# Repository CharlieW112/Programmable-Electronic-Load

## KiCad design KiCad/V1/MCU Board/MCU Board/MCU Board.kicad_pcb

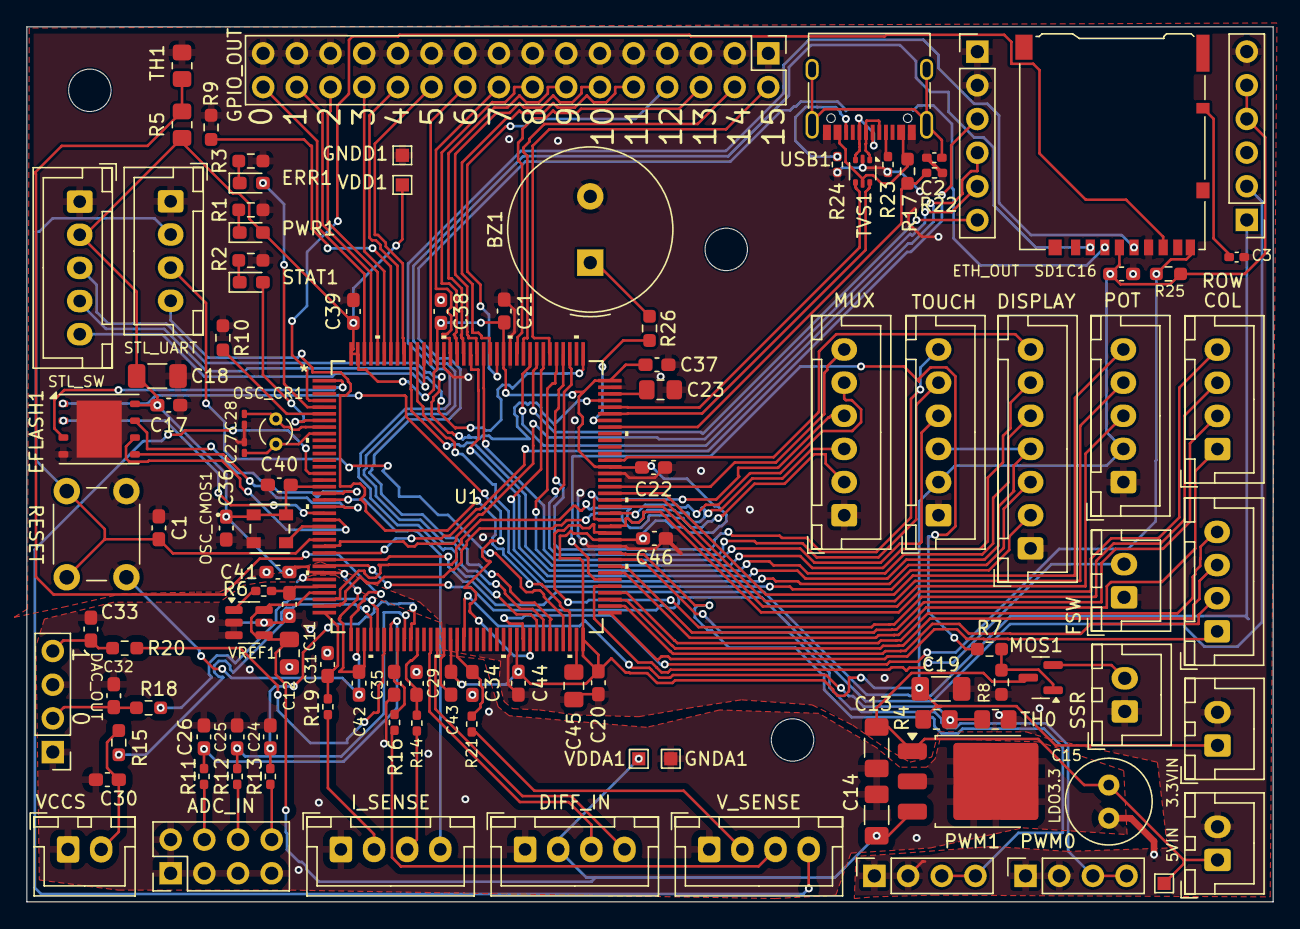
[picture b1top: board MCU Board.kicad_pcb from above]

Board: 2 copper layers, 94.0 x 66.0 mm, 114 parts (0 on the bottom side), 127 nets.

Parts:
3.3VIN, 5VIN: Conn_01x02; JST_XH_B2B-XH-A_1x02_P2.50mm_Vertical
5VIN2: TestPoint; TestPoint_Pad_1.0x1.0mm
ADC_IN: Conn_02x04_Odd_Even; PinHeader_2x04_P2.54mm_Vertical
BZ1: Buzzer; Buzzer_TDK_PS1240P02BT_D12.2mm_H6.5mm
C1: 100n; C_0603_1608Metric_Pad1.08x0.95mm_HandSolder
C2, C3: 10n; C_0402_1005Metric_Pad0.74x0.62mm_HandSolder
C11, C16, C17, C21, C22, C24, C25, C26, C29, C30, C31, C32, C33, C34, C35, C36, C37, C38, C39, C40, C41, C42, C43, C44, C45, C46: 0.1u; C_0603_1608Metric_Pad1.08x0.95mm_HandSolder
C12, C20, C23: 1u; C_0805_2012Metric_Pad1.18x1.45mm_HandSolder
C13, C14, C18, C19: 10u; C_1206_3216Metric_Pad1.33x1.80mm_HandSolder
C15: 100u; C_Radial_D6.3mm_H11.0mm_P2.50mm
C27, C28: 10p; C_0201_0603Metric_Pad0.64x0.40mm_HandSolder
COL: Conn_01x04; JST_XH_B4B-XH-A_1x04_P2.50mm_Vertical
DAC_OUT: Conn_01x04; PinHeader_1x04_P2.54mm_Vertical
DIFF_IN: Conn_01x04; JST_XH_B4B-XH-A_1x04_P2.50mm_Vertical
DISPLAY: Conn_01x07; JST_XH_B7B-XH-A_1x07_P2.50mm_Vertical
EFLASH1: W25Q128JVP; WSON-8-1EP_6x5mm_P1.27mm_EP3.4x4.3mm
ERR1: Red LED; D_0603_1608Metric_Pad1.05x0.95mm_HandSolder
ETH_OUT, ETH_OUT1: Conn_01x06; PinHeader_1x06_P2.54mm_Vertical
FSW: Conn_01x02; JST_XH_B2B-XH-A_1x02_P2.50mm_Vertical
GNDA1: TestPoint; TestPoint_Pad_1.0x1.0mm
GNDD1: TestPoint; TestPoint_Pad_1.0x1.0mm
GPIO_OUT: Conn_02x16_Odd_Even; PinHeader_2x16_P2.54mm_Vertical
H1, H2, H3: MountingHole; MountingHole_3.2mm_M3
I_SENSE: Conn_01x04; JST_XH_B4B-XH-A_1x04_P2.50mm_Vertical
LDO3.3: TO-252-3_TabPin2
MOS1: AO3400A; SOT-23
MUX: Conn_01x06; JST_XH_B6B-XH-A_1x06_P2.50mm_Vertical
NT1: NetTie_2; NetTie-2_SMD_Pad0.5mm
OSC_CMOS1: COM1305-25.000; SMD4_COM1305_2p5x3p2x1p0_RAL-M
OSC_CR1: AB26T-32.768KHZ; Crystal_C26-LF_D2.1mm_L6.5mm_Vertical
POT: Conn_01x05; JST_XH_B5B-XH-A_1x05_P2.50mm_Vertical
PWM0, PWM1: Conn_01x04; PinSocket_1x04_P2.54mm_Vertical
PWR1: Green LED; D_0603_1608Metric_Pad1.05x0.95mm_HandSolder
R1, R2, R3, R7: 1K; R_0603_1608Metric_Pad0.98x0.95mm_HandSolder
R4, R5: 10K 0.5%; R_0805_2012Metric_Pad1.20x1.40mm_HandSolder
R6: 10; R_0402_1005Metric_Pad0.72x0.64mm_HandSolder
R8, R10, R17, R25: 10K; R_0603_1608Metric_Pad0.98x0.95mm_HandSolder
R9: 10k; R_0603_1608Metric_Pad0.98x0.95mm_HandSolder
R11, R12, R13, R14, R16, R19, R21: 49.9; R_0402_1005Metric_Pad0.72x0.64mm_HandSolder
R15, R18, R20, R26: 100; R_0603_1608Metric_Pad0.98x0.95mm_HandSolder
R22: 20K; R_0402_1005Metric_Pad0.72x0.64mm_HandSolder
R23, R24: 5.1K; R_0402_1005Metric_Pad0.72x0.64mm_HandSolder
RESET: SW_Push; SW_PUSH_6mm_H9.5mm
ROW: Conn_01x04; JST_XH_B4B-XH-A_1x04_P2.50mm_Vertical
SD1: Micro_SD_Card_Det1; microSD_HC_Hirose_DM3AT-SF-PEJM5
SSR: Conn_01x02; JST_XH_B2B-XH-A_1x02_P2.50mm_Vertical
STAT1: Green LED; D_0603_1608Metric_Pad1.05x0.95mm_HandSolder
STL_SW: Conn_01x05; JST_XH_B5B-XH-A_1x05_P2.50mm_Vertical
STL_UART: Conn_01x04; JST_XH_B4B-XH-A_1x04_P2.50mm_Vertical
TH0, TH1: Thermistor_NTC; R_0805_2012Metric_Pad1.20x1.40mm_HandSolder
TOUCH: Conn_01x06; JST_XH_B6B-XH-A_1x06_P2.50mm_Vertical
TVS1: USBLC6-2P6; SOT-666
U1: STM32H7A3ZIT6; LQFP-144-M
USB1: USB_C_Receptacle_USB2.0_16P; USB_C_Receptacle_XKB_U262-16XN-4BVC11
VCCS: Conn_01x02; JST_XH_B2B-XH-A_1x02_P2.50mm_Vertical
VDD1: TestPoint; TestPoint_Pad_1.0x1.0mm
VDDA1: TestPoint; TestPoint_Pad_1.0x1.0mm
VREF1: MCP1501-33xCH; SOT-23-6
V_SENSE: Conn_01x04; JST_XH_B4B-XH-A_1x04_P2.50mm_Vertical

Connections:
3.3VREF: C11.1, R6.2, U1.32 (VREF+)
+5V: 5VIN.1, 5VIN2.1, C13.1, C15.1, LDO3.3.1 (IN), MOS1.3 (D)
/USB+: TVS1.3 (I/O2), USB1.A6 (D+), USB1.B6 (D+)
/USB-: TVS1.1 (I/O1), USB1.A7 (D-), USB1.B7 (D-)
ADC0_UNUSED: C26.1, R11.2, U1.43 (ADC0_UNUSED)
ADC1_UNUSED: C25.1, R12.2, U1.45 (ADC1_UNUSED)
ADC2_UNUSED: C24.1, R13.2, U1.46 (ADC2_UNUSED)
ADC_DIFF_N: DIFF_IN.4, U1.50 (ADC_DIFF_N)
ADC_DIFF_P: DIFF_IN.3, U1.49 (ADC_DIFF_P)
ADC_ISENSEC: C29.2, R14.1, U1.47 (ADC_ISENSEC)
ADC_ISENSEF: C31.1, R19.1, U1.36 (ADC_ISENSEF)
ADC_VCCSSENSE: C35.2, R16.1, U1.44 (ADC_VCCSSENSE)
ADC_VSENSE: C34.1, R21.1, U1.53 (ADC_VSENSE)
DAC0_UNUSED: R18.1, U1.41 (DAC0_UNUSED)
DAC1_UNUSED: R20.1, U1.42 (DAC1_UNUSED)
DAC_VCCS: R15.1, U1.40 (DAC_VCCS)
DISPL_CS: DISPLAY.2, U1.134 (DISPL_CS)
DISPL_DC: DISPLAY.6, U1.113 (DISPL_DC)
DISPL_LED: DISPLAY.7, U1.96 (DISPL_LED)
DISPL_MOSI: DISPLAY.5, U1.135 (DISPL_MOSI)
DISPL_RST: DISPLAY.3, U1.115 (DISPL_RST)
DISPL_SCK: DISPLAY.4, TOUCH.3, U1.126 (DISPL_SCK)
DTH2: R4.2, TH0.1, U1.54 (DTH2)
DTH3: R5.2, TH1.1, U1.37 (DTH3)
ENCODER_A: POT.3, U1.89 (ENCODER_A)
ENCODER_B: POT.4, U1.90 (ENCODER_B)
ENCODER_SW: POT.5, U1.91 (ENCODER_SW)
ERROR_LED: ERR1.2 (A), U1.5 (ERROR_LED)
ETH_CS: ETH_OUT.5, U1.26 (ETH_CS)
ETH_INT: ETH_OUT.6, U1.116 (ETH_INT)
ETH_MISO: ETH_OUT1.1, U1.28 (ETH_MISO)
ETH_MOSI: ETH_OUT.3, U1.27 (ETH_MOSI)
ETH_RST: ETH_OUT1.2, U1.29 (ETH_RST)
ETH_SCK: ETH_OUT.4, U1.117 (ETH_SCK)
E_FLASH_CLK: EFLASH1.6 (CLK), U1.22 (E_FLASH_CLK)
E_FLASH_CS: EFLASH1.1 (~CS), U1.64 (E_FLASH_CS)
E_FLASH_IO0: EFLASH1.5 (DI/IO_{0}), U1.20 (E_FLASH_IO0)
E_FLASH_IO1: EFLASH1.2 (DO/IO_{1}), U1.21 (E_FLASH_IO1)
E_FLASH_IO2: EFLASH1.3 (~WP/IO_{2}), U1.1 (E_FLASH_IO2)
E_FLASH_IO3: EFLASH1.7 (~HOLD/~RESET/IO_{3}), U1.18 (E_FLASH_IO3)
FRONT_SW: FSW.2, U1.77 (FRONT_SW)
GNDA: ADC_IN.1, ADC_IN.2, ADC_IN.3, ADC_IN.5, ADC_IN.7, C11.2, C12.2, C13.2, C14.2, C15.2, C24.2, C25.2, C26.2, C29.1, C30.1, C31.2, C32.1, C33.2, C34.2, C35.1, DAC_OUT.1, DAC_OUT.3, DIFF_IN.1, GNDA1.1, I_SENSE.1, LDO3.3.2 (GND), NT1.2, U1.31 (VSSA), VCCS.1, VREF1.2 (GND), VREF1.3 (GND), VREF1.5 (GND), V_SENSE.1
GNDD: 3.3VIN.2, 5VIN.2, BZ1.2 (-), C1.2, C2.2, C3.2, C16.1, C17.2, C18.2, C19.2, C20.2, C21.2, C22.2, C23.2, C27.2, C28.2, C36.2, C37.1, C38.1, C39.1, C40.1, C41.1, C42.1, C43.1, C44.1, C45.1, C46.1, DISPLAY.1, EFLASH1.4 (GND), EFLASH1.9 (EP), ETH_OUT.1, ETH_OUT.2, ETH_OUT1.6, FSW.1, GNDD1.1, GPIO_OUT.1, GPIO_OUT.3, GPIO_OUT.5, GPIO_OUT.7, GPIO_OUT.9, GPIO_OUT.11, GPIO_OUT.13, GPIO_OUT.15, GPIO_OUT.17, GPIO_OUT.19, GPIO_OUT.21, GPIO_OUT.23, GPIO_OUT.25, GPIO_OUT.27, GPIO_OUT.29, GPIO_OUT.31, MUX.1, NT1.1, OSC_CMOS1.2 (GND), POT.1, PWM0.1, PWM0.2, PWM1.1, PWM1.2, R1.2, R2.2, R3.2, R8.2, R9.2, R10.1, R22.2, R23.2, R24.2, RESET.2, SD1.6 (VSS), SSR.1, STL_SW.1, STL_UART.1, TH0.2, TH1.2, TOUCH.1, TVS1.2 (GND), U1.16 (VSS), U1.38 (VSS), U1.51 (VSS), U1.61 (VSS), U1.83 (VSS), U1.94 (VSS), U1.107 (VSS), U1.120 (VSS), U1.130 (VSS), USB1.A1 (GND), USB1.A12 (GND), USB1.B1 (GND), USB1.B12 (GND)
GPIO0_UNUSED: GPIO_OUT.32, U1.142 (GPIO0_UNUSED)
GPIO1_UNUSED: GPIO_OUT.30, U1.141 (GPIO1_UNUSED)
GPIO2_UNUSED: GPIO_OUT.28, U1.140 (GPIO2_UNUSED)
GPIO3_UNUSED: GPIO_OUT.26, U1.139 (GPIO3_UNUSED)
GPIO4_UNUSED: GPIO_OUT.24, U1.137 (GPIO4_UNUSED)
GPIO5_UNUSED: GPIO_OUT.22, U1.136 (GPIO5_UNUSED)
GPIO6_UNUSED: GPIO_OUT.20, U1.132 (GPIO6_UNUSED)
GPIO7_UNUSED: GPIO_OUT.18, U1.129 (GPIO7_UNUSED)
GPIO8_UNUSED: GPIO_OUT.16, U1.128 (GPIO8_UNUSED)
GPIO9_UNUSED: GPIO_OUT.14, U1.127 (GPIO9_UNUSED)
GPIO10_UNUSED: GPIO_OUT.12, U1.125 (GPIO10_UNUSED)
GPIO11_UNUSED: GPIO_OUT.10, U1.123 (GPIO11_UNUSED)
GPIO12_UNUSED: GPIO_OUT.8, U1.122 (GPIO12_UNUSED)
GPIO13_UNUSED: GPIO_OUT.6, U1.119 (GPIO13_UNUSED)
GPIO14_UNUSED: GPIO_OUT.4, U1.118 (GPIO14_UNUSED)
GPIO15_UNUSED: GPIO_OUT.2, U1.114 (GPIO15_UNUSED)
GPIO_I_SENSE_EN: I_SENSE.4, U1.19 (PF7)
GPIO_WARNING_HV: U1.15 (PF5), V_SENSE.4
HSE_OSC: OSC_CMOS1.3 (OUT), U1.23 (HSE_OSC)
MATC0: COL.1, U1.73 (MATC0)
MATC1: COL.2, U1.74 (MATC1)
MATC2: COL.3, U1.75 (MATC2)
MATC3: COL.4, U1.76 (MATC3)
MATR0: ROW.1, U1.79 (MATR0)
MATR1: ROW.2, U1.80 (MATR1)
MATR2: ROW.3, U1.85 (MATR2)
MATR3: ROW.4, U1.86 (MATR3)
MUX_A: MUX.4, U1.87 (PG2)
MUX_B: MUX.5, U1.88 (PG3)
MUX_C: MUX.6, U1.92 (PG7)
MUX_TH0: MUX.2, U1.35 (MUX_TH0)
MUX_TH1: MUX.3, U1.34 (MUX_TH1)
NRST: C1.1, RESET.1, STL_UART.2, U1.25 (NRST)
unnamed: ADC_IN.4, R11.1
unnamed: ADC_IN.6, R12.1
unnamed: ADC_IN.8, R13.1
unnamed: BZ1.1 (+), R26.2
unnamed: C32.2, DAC_OUT.2, R18.2
unnamed: C33.1, DAC_OUT.4, R20.2
unnamed: ERR1.1 (K), R3.1
unnamed: I_SENSE.2, R19.2
unnamed: I_SENSE.3, R14.2
unnamed: MOS1.1 (G), R7.2, R8.1
unnamed: PWR1.1 (K), R1.1
unnamed: C3.1, SD1.10 (SHIELD)
unnamed: R2.1, STAT1.1 (K)
unnamed: R17.1, TVS1.5 (VBUS), USB1.A4 (VBUS), USB1.A9 (VBUS), USB1.B4 (VBUS), USB1.B9 (VBUS)
unnamed: R10.2, U1.6 (VBAT)
unnamed: C20.1, U1.71 (VCAP)
unnamed: R9.1, U1.138 (BOOT0)
unnamed: C23.1, U1.106 (VCAP)
unnamed: R23.1, USB1.A5 (CC1)
unnamed: R24.1, USB1.B5 (CC2)
unnamed: C2.1, USB1.S1 (SHIELD)
unnamed: C30.2, R15.2, VCCS.2
unnamed: R6.1, VREF1.1 (OUT)
unnamed: R21.2, V_SENSE.2
unnamed: R16.2, V_SENSE.3
PWM0: PWM0.3, PWM0.4, U1.81 (PWM0)
PWM1: PWM1.3, PWM1.4, U1.82 (PWM1)
PWM_BUZZER: R26.1, U1.102 (PA10)
RTC_OSC_IN: C28.1, OSC_CR1.1, U1.8 (RTC_OSC_IN)
RTC_OSC_OUT: C27.1, OSC_CR1.2, U1.9 (RTC_OSC_OUT)
SD_CARD_DETECT: R25.1, SD1.9 (DET), U1.63 (SD_CARD_DETECT)
SD_CS: SD1.2 (DAT3/CD), U1.66 (SD_CS)
SD_MISO: SD1.7 (DAT0), U1.4 (SD_MISO)
SD_MOSI: SD1.3 (CMD), U1.67 (SD_MOSI)
SD_SCK: SD1.5 (CLK), U1.65 (SD_SCK)
SSR_EN: R7.1, U1.78 (SSR_EN)
SSR_OUT: MOS1.2 (S), SSR.2
STATUS_LED: STAT1.2 (A), U1.7 (STATUS_LED)
ST_LINK_RX: STL_UART.4, U1.70 (ST_LINK_RX)
ST_LINK_SWCLK: STL_SW.4, U1.109 (ST_LINK_SWCLK)
ST_LINK_SWDIO: STL_SW.3, U1.105 (ST_LINK_SWDIO)
ST_LINK_SWO: STL_SW.5, U1.133 (ST_LINK_SWO)
ST_LINK_TX: STL_UART.3, U1.69 (ST_LINK_TX)
TOUCH_CS: TOUCH.5, U1.111 (TOUCH_CS)
TOUCH_INT: TOUCH.6, U1.112 (TOUCH_INT)
TOUCH_MISO: TOUCH.4, U1.124 (TOUCH_MISO)
USB_DM: TVS1.6 (I/O1), U1.103 (USB_DM)
USB_DP: TVS1.4 (I/O2), U1.104 (USB_DP)
USB_VBUS: R17.2, R22.1, U1.101 (USB_VBUS)
VDD: 3.3VIN.1, C16.2, C17.1, C18.1, C19.1, C21.1, C22.1, C36.1, C37.2, C38.2, C39.2, C40.2, C41.2, C42.2, C43.2, C44.2, C45.2, C46.2, EFLASH1.8 (VCC), ETH_OUT1.4, ETH_OUT1.5, OSC_CMOS1.1 (EN), OSC_CMOS1.4 (Vdd), POT.2, PWR1.2 (A), R4.1, R5.1, R25.2, SD1.4 (VDD), STL_SW.2, TOUCH.2, U1.17 (VDD), U1.30 (VDD), U1.39 (VDD), U1.52 (VDD), U1.62 (VDD), U1.72 (VDD), U1.84 (VDD), U1.95 (VDD33USB), U1.108 (VDD), U1.121 (VDDMMC), U1.131 (VDD), U1.143 (PDR_ON), U1.144 (VDD), VDD1.1
VDDA: C12.1, C14.1, DIFF_IN.2, LDO3.3.3 (OUT), U1.33 (VDDA), VDDA1.1, VREF1.4 (~SHDN), VREF1.6 (VDD)

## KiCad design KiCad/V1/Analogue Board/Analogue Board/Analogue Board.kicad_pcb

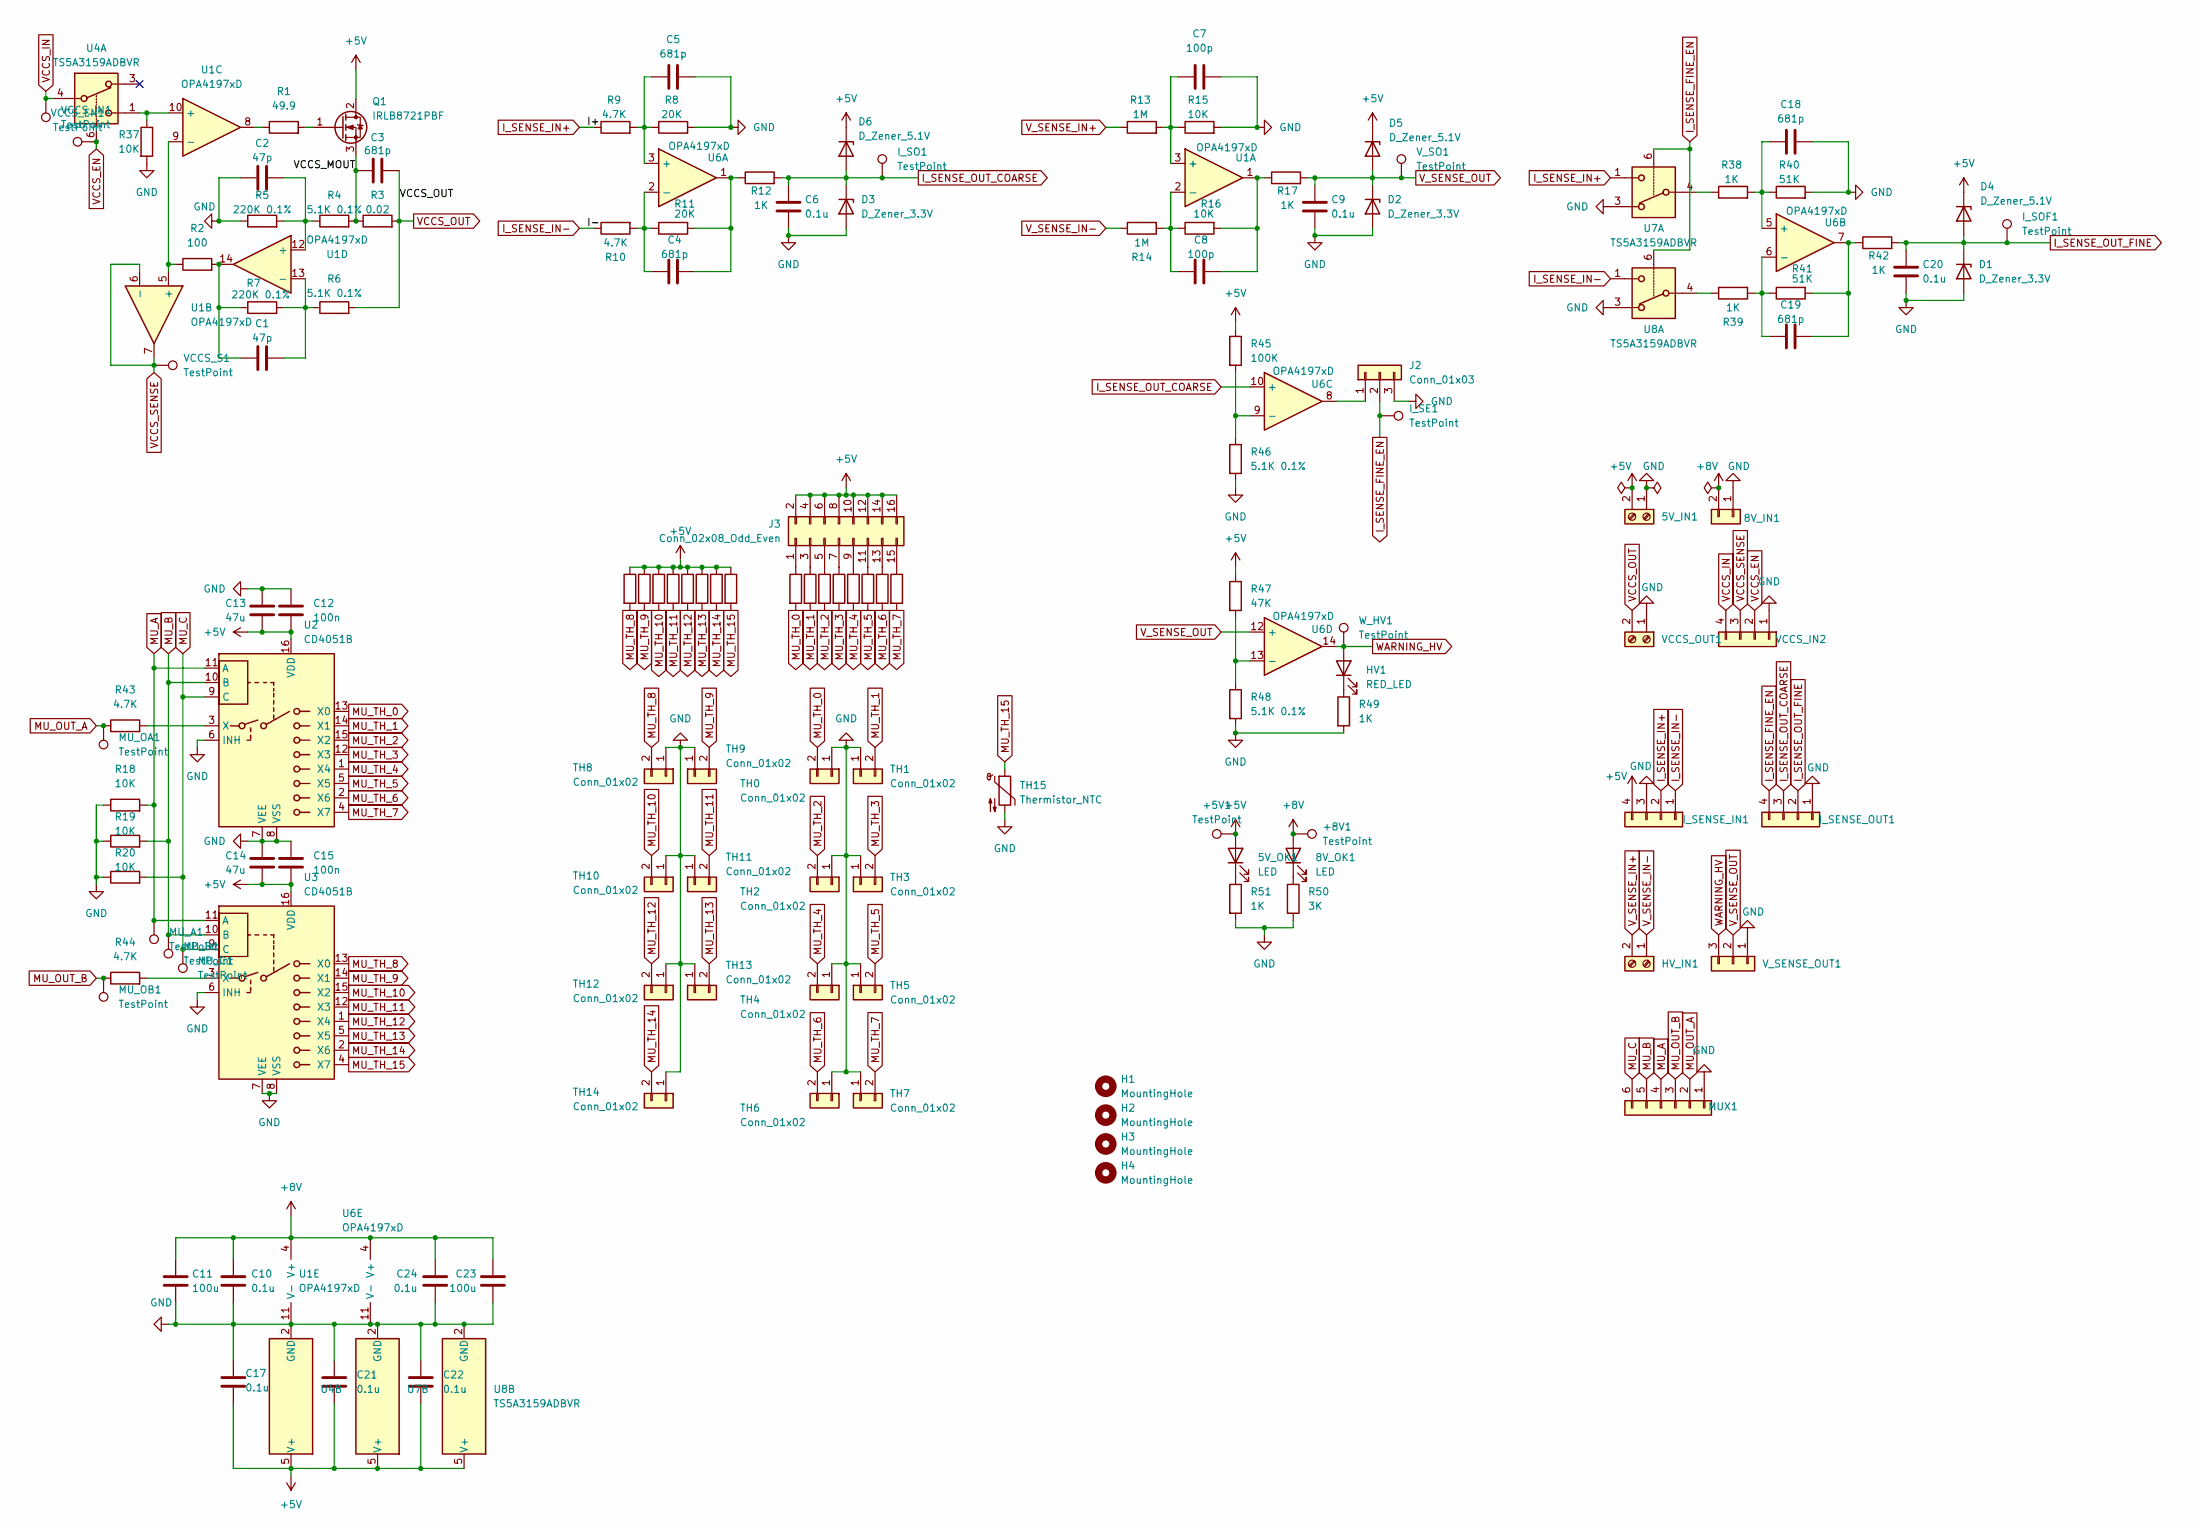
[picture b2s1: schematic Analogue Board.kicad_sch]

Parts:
5V_IN1: Screw_Terminal_01x02; TerminalBlock_bornier-2_P5.08mm
5V_OK1, 8V_OK1: LED; D_0603_1608Metric_Pad1.05x0.95mm_HandSolder
8V_IN1: Conn_01x02; JST_XH_B2B-XH-A_1x02_P2.50mm_Vertical
+5V1, +8V1: TestPoint; TestPoint_Pad_1.5x1.5mm
C1, C2: 47p; C_0201_0603Metric_Pad0.64x0.40mm_HandSolder
C3, C4, C5, C18, C19: 681p; C_0201_0603Metric_Pad0.64x0.40mm_HandSolder
C6, C9, C10, C17, C20, C21, C22, C24: 0.1u; C_0603_1608Metric_Pad1.08x0.95mm_HandSolder
C7, C8: 100p; C_0402_1005Metric_Pad0.74x0.62mm_HandSolder
C11, C23: 100u; C_Radial_D6.3mm_H11.0mm_P2.50mm
C12, C15: 100n; C_0603_1608Metric_Pad1.08x0.95mm_HandSolder
C13, C14: 47u; C_Radial_D6.3mm_H11.0mm_P2.50mm
D1, D2, D3: D_Zener_3.3V; D_SOD-123
D4, D5, D6: D_Zener_5.1V; D_SOD-123
H1, H2, H3, H4: MountingHole; MountingHole_3.2mm_M3
HV1: RED_LED; D_0603_1608Metric_Pad1.05x0.95mm_HandSolder
HV_IN1: Screw_Terminal_01x02; TerminalBlock_bornier-2_P5.08mm
I_SE1: TestPoint; TestPoint_Pad_1.5x1.5mm
I_SENSE_IN1: Conn_01x04; JST_XH_B4B-XH-A_1x04_P2.50mm_Vertical
I_SENSE_OUT1: Conn_01x04; JST_XH_B4B-XH-A_1x04_P2.50mm_Vertical
I_SO1: TestPoint; TestPoint_Pad_1.5x1.5mm
I_SOF1: TestPoint; TestPoint_Pad_1.5x1.5mm
J2: Conn_01x03; PinHeader_1x03_P2.54mm_Vertical
J3: Conn_02x08_Odd_Even; PinHeader_2x08_P2.54mm_Vertical
MUX1: Conn_01x06; JST_XH_B6B-XH-A_1x06_P2.50mm_Vertical
MU_A1: TestPoint; TestPoint_Pad_1.5x1.5mm
MU_B1: TestPoint; TestPoint_Pad_1.5x1.5mm
MU_C1: TestPoint; TestPoint_Pad_1.5x1.5mm
MU_OA1: TestPoint; TestPoint_Pad_1.5x1.5mm
MU_OB1: TestPoint; TestPoint_Pad_1.5x1.5mm
Q1: IRLB8721PBF; TO-220-3_Vertical
R1: 49.9; R_0402_1005Metric_Pad0.72x0.64mm_HandSolder
R2: 100; R_0603_1608Metric_Pad0.98x0.95mm_HandSolder
R3: 0.02; R_2010_5025Metric_Pad1.40x2.65mm_HandSolder
R4, R6, R46, R48: 5.1K 0.1%; R_0603_1608Metric_Pad0.98x0.95mm_HandSolder
R5, R7: 220K 0.1%; R_0805_2012Metric_Pad1.20x1.40mm_HandSolder
R8, R11: 20K; R_0402_1005Metric_Pad0.72x0.64mm_HandSolder
R9, R10, R43, R44: 4.7K; R_0603_1608Metric_Pad0.98x0.95mm_HandSolder
R12, R17, R38, R39, R42, R49, R51: 1K; R_0603_1608Metric_Pad0.98x0.95mm_HandSolder
R13, R14: 1M; R_Axial_DIN0207_L6.3mm_D2.5mm_P7.62mm_Horizontal
R15, R16, R18, R19, R20, R37: 10K; R_0603_1608Metric_Pad0.98x0.95mm_HandSolder
R21, R22, R23, R24, R25, R26, R27, R28, R29, R30, R31, R32, R33, R34, R35, R36: 10K 0.5%; R_0805_2012Metric_Pad1.20x1.40mm_HandSolder
R40, R41: 51K; R_0603_1608Metric_Pad0.98x0.95mm_HandSolder
R45: 100K; R_0402_1005Metric_Pad0.72x0.64mm_HandSolder
R47: 47K; R_0603_1608Metric_Pad0.98x0.95mm_HandSolder
R50: 3K; R_0603_1608Metric_Pad0.98x0.95mm_HandSolder
TH0, TH1, TH2, TH3, TH4, TH5, TH6, TH7, TH8, TH9, TH10, TH11, TH12, TH13, TH14: Conn_01x02; JST_XH_B2B-XH-A_1x02_P2.50mm_Vertical
TH15: Thermistor_NTC; R_0805_2012Metric_Pad1.20x1.40mm_HandSolder
U1, U6: OPA4197xD; SOIC-14_3.9x8.7mm_P1.27mm
U2, U3: CD4051B; DIP-16_W7.62mm
U4, U7, U8: TS5A3159ADBVR; SOT-23-6
VCCS_EN1: TestPoint; TestPoint_Pad_1.5x1.5mm
VCCS_IN1: TestPoint; TestPoint_Pad_1.5x1.5mm
VCCS_IN2: Conn_01x04; JST_XH_B4B-XH-A_1x04_P2.50mm_Vertical
VCCS_OUT1: Screw_Terminal_01x02; TerminalBlock_bornier-2_P5.08mm
VCCS_S1: TestPoint; TestPoint_Pad_1.5x1.5mm
V_SENSE_OUT1: Conn_01x03; JST_XH_B3B-XH-A_1x03_P2.50mm_Vertical
V_SO1: TestPoint; TestPoint_Pad_1.5x1.5mm
W_HV1: TestPoint; TestPoint_Pad_1.5x1.5mm

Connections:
+5V: 5V_IN1.2, 5V_OK1.2 (A), +5V1.1, C12.2, C13.2, C14.2, C15.2, C17.2, C21.2, C22.2, D4.1 (K), D5.1 (K), D6.1 (K), I_SENSE_IN1.4, J3.2, J3.4, J3.6, J3.8, J3.10, J3.12, J3.14, J3.16, Q1.2 (D), R29.1, R30.1, R31.1, R32.1, R33.1, R34.1, R35.1, R36.1, R45.1, R47.1, U2.16 (VDD), U3.16 (VDD), U4.5 (V+), U7.5 (V+), U8.5 (V+)
+8V: 8V_IN1.2, 8V_OK1.2 (A), +8V1.1, C10.1, C11.1, C23.1, C24.1, U1.4 (V+), U6.4 (V+)
/VCCS_MOUT: C3.1, Q1.3 (S), R3.1, R4.2
GND: 5V_IN1.1, 8V_IN1.1, C2.1, C5.2, C6.2, C7.2, C9.2, C10.2, C11.2, C12.1, C13.1, C14.1, C15.1, C17.1, C18.2, C20.2, C21.1, C22.1, C23.2, C24.2, D1.2 (A), D2.2 (A), D3.2 (A), I_SENSE_IN1.3, I_SENSE_OUT1.1, J2.3, MUX1.1, R5.1, R8.2, R15.2, R18.1, R19.1, R20.1, R37.2, R40.2, R46.2, R48.2, R49.2, R50.2, R51.2, TH0.1, TH1.1, TH2.1, TH3.1, TH4.1, TH5.1, TH6.1, TH7.1, TH8.1, TH9.1, TH10.1, TH11.1, TH12.1, TH13.1, TH14.1, TH15.2, U1.11 (V-), U2.6 (INH), U2.7 (VEE), U2.8 (VSS), U3.6 (INH), U3.7 (VEE), U3.8 (VSS), U4.2 (GND), U6.11 (V-), U7.2 (GND), U7.3, U8.2 (GND), U8.3, VCCS_IN2.1, VCCS_OUT1.1, V_SENSE_OUT1.1
I_SENSE_FINE_EN: I_SE1.1, I_SENSE_OUT1.4, J2.2, U7.6, U8.6
I_SENSE_IN+: I_SENSE_IN1.2, R9.1, U7.1
I_SENSE_IN-: I_SENSE_IN1.1, R10.1, U8.1
I_SENSE_OUT_COARSE: C6.1, D3.1 (K), D6.2 (A), I_SENSE_OUT1.3, I_SO1.1, R12.2, U6.10 (+)
I_SENSE_OUT_FINE: C20.1, D1.1 (K), D4.2 (A), I_SENSE_OUT1.2, I_SOF1.1, R42.2
MU_A: MUX1.4, MU_A1.1, R18.2, U2.11 (A), U3.11 (A)
MU_B: MUX1.5, MU_B1.1, R19.2, U2.10 (B), U3.10 (B)
MU_C: MUX1.6, MU_C1.1, R20.2, U2.9 (C), U3.9 (C)
MU_OUT_A: MUX1.2, MU_OA1.1, R43.1
MU_OUT_B: MUX1.3, MU_OB1.1, R44.1
MU_TH_0: R21.2, TH0.2, U2.13 (X0)
MU_TH_1: R22.2, TH1.2, U2.14 (X1)
MU_TH_2: R23.2, TH2.2, U2.15 (X2)
MU_TH_3: R24.2, TH3.2, U2.12 (X3)
MU_TH_4: R25.2, TH4.2, U2.1 (X4)
MU_TH_5: R26.2, TH5.2, U2.5 (X5)
MU_TH_6: R27.2, TH6.2, U2.2 (X6)
MU_TH_7: R28.2, TH7.2, U2.4 (X7)
MU_TH_8: R29.2, TH8.2, U3.13 (X0)
MU_TH_9: R30.2, TH9.2, U3.14 (X1)
MU_TH_10: R31.2, TH10.2, U3.15 (X2)
MU_TH_11: R32.2, TH11.2, U3.12 (X3)
MU_TH_12: R33.2, TH12.2, U3.1 (X4)
MU_TH_13: R34.2, TH13.2, U3.5 (X5)
MU_TH_14: R35.2, TH14.2, U3.2 (X6)
MU_TH_15: R36.2, TH15.1, U3.4 (X7)
unnamed: 5V_OK1.1 (K), R51.1
unnamed: 8V_OK1.1 (K), R50.1
unnamed: C1.1, R2.2, R7.1, U1.14
unnamed: C4.2, R11.2, R12.1, U6.1
unnamed: C8.2, R16.2, R17.1, U1.1
unnamed: C19.2, R41.2, R42.1, U6.7
unnamed: HV1.1 (K), R49.1
unnamed: J2.1, U6.8
unnamed: J3.1, R21.1
unnamed: J3.3, R22.1
unnamed: J3.5, R23.1
unnamed: J3.7, R24.1
unnamed: J3.9, R25.1
unnamed: J3.11, R26.1
unnamed: J3.13, R27.1
unnamed: J3.15, R28.1
unnamed: Q1.1 (G), R1.2
unnamed: R1.1, U1.8
unnamed: R38.1, U7.4
unnamed: R39.1, U8.4
unnamed: C7.1, R13.2, R15.1, U1.3 (+)
unnamed: C8.1, R14.2, R16.1, U1.2 (-)
unnamed: R2.1, U1.5 (+), U1.9 (-)
unnamed: R37.1, U1.10 (+), U4.1
unnamed: C2.2, R4.1, R5.2, U1.12 (+)
unnamed: C1.2, R6.1, R7.2, U1.13 (-)
unnamed: R43.2, U2.3 (X)
unnamed: R44.2, U3.3 (X)
unnamed: C5.1, R8.1, R9.2, U6.3 (+)
unnamed: C4.1, R10.2, R11.1, U6.2 (-)
unnamed: C18.1, R38.2, R40.1, U6.5 (+)
unnamed: C19.1, R39.2, R41.1, U6.6 (-)
unnamed: R45.2, R46.1, U6.9 (-)
unnamed: R47.2, R48.1, U6.13 (-)
VCCS_EN: U4.6, VCCS_EN1.1, VCCS_IN2.2
VCCS_IN: U4.4, VCCS_IN1.1, VCCS_IN2.4
VCCS_OUT: C3.2, R3.2, R6.2, VCCS_OUT1.2
VCCS_SENSE: U1.6 (-), U1.7, VCCS_IN2.3, VCCS_S1.1
V_SENSE_IN+: HV_IN1.2, R13.1
V_SENSE_IN-: HV_IN1.1, R14.1
V_SENSE_OUT: C9.1, D2.1 (K), D5.2 (A), R17.2, U6.12 (+), V_SENSE_OUT1.2, V_SO1.1
WARNING_HV: HV1.2 (A), U6.14, V_SENSE_OUT1.3, W_HV1.1

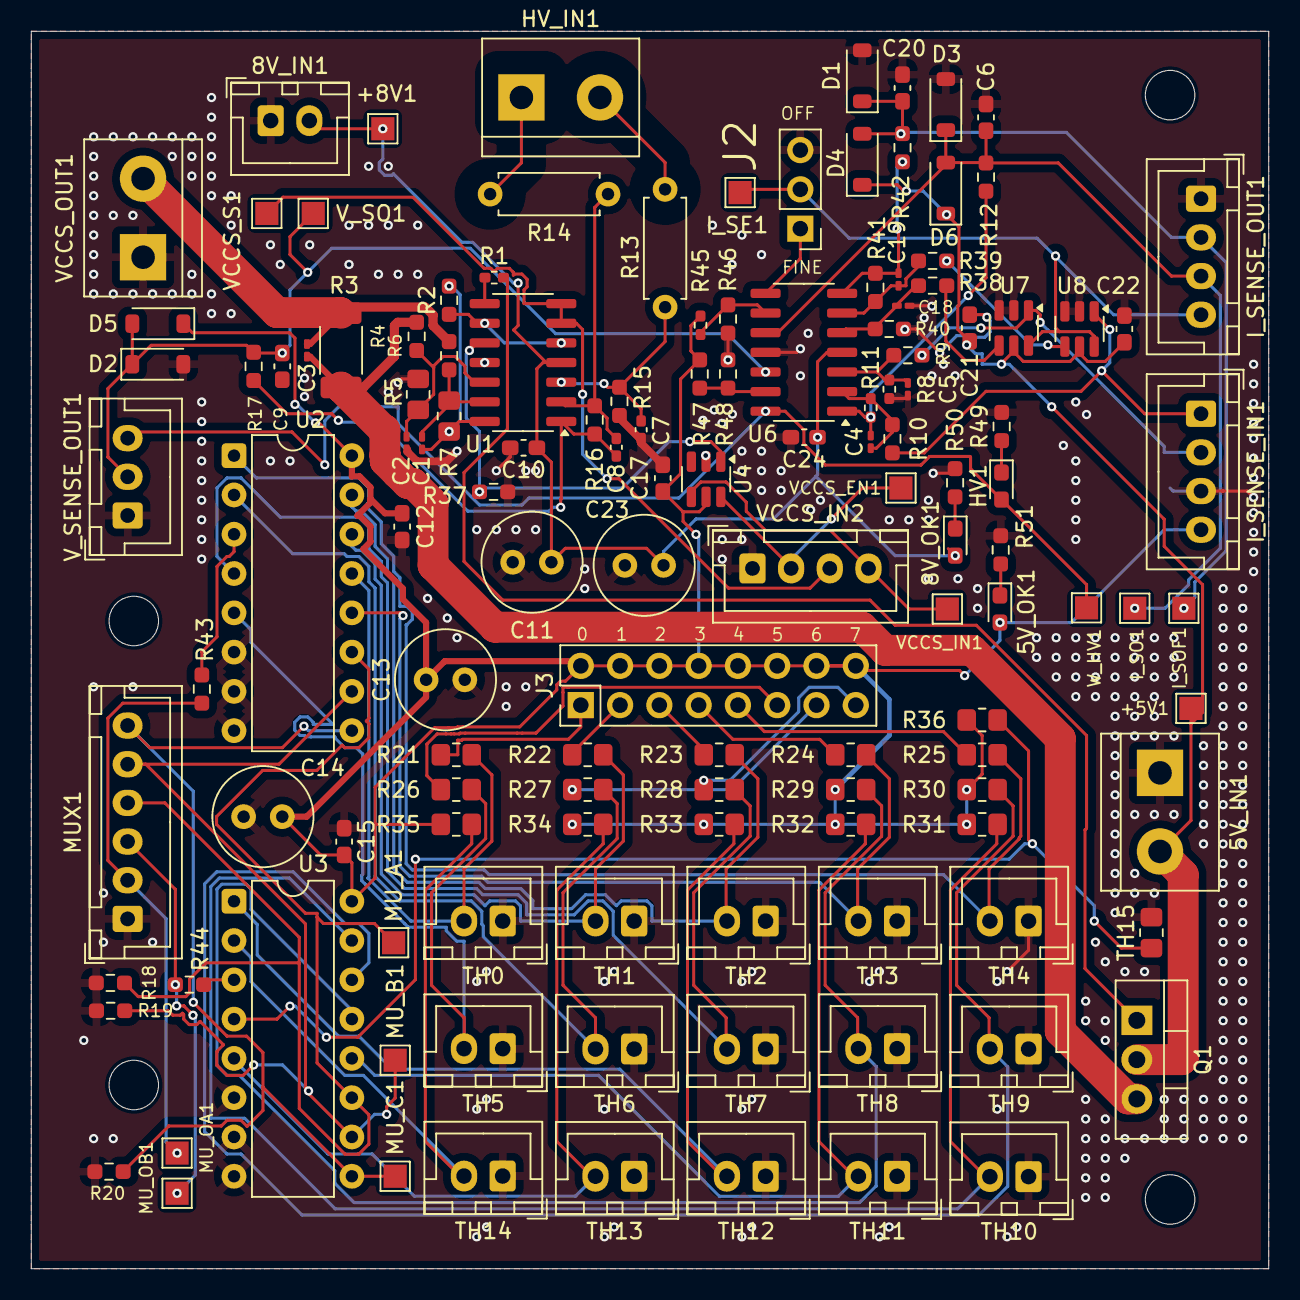
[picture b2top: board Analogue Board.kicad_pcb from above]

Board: 2 copper layers, 80.0 x 80.0 mm, 137 parts (0 on the bottom side), 72 nets.

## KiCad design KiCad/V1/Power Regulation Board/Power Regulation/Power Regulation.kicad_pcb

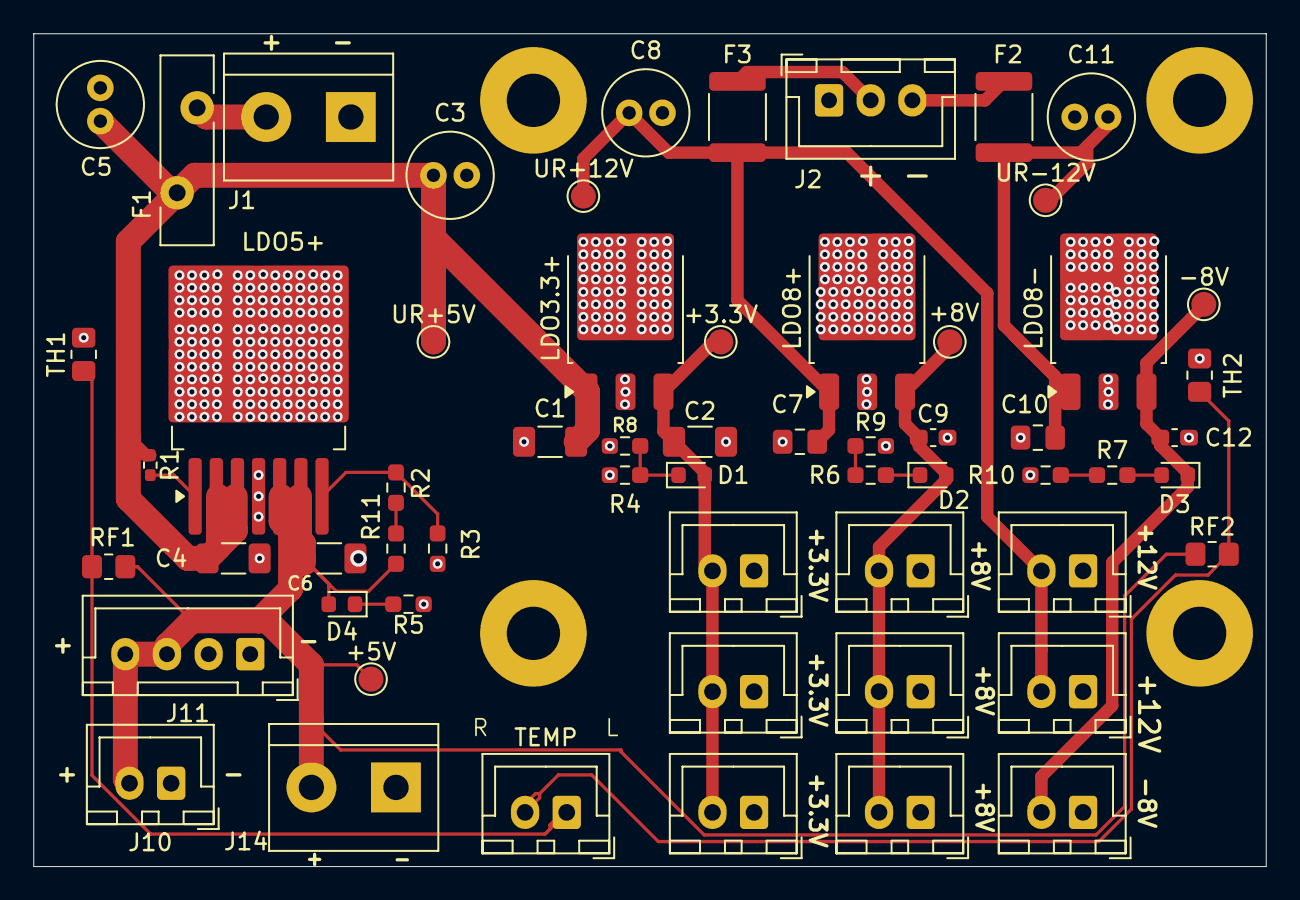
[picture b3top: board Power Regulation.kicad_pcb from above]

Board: 2 copper layers, 74.0 x 50.0 mm, 64 parts (0 on the bottom side), 22 nets.

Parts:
+3.3V, +5V, +8V: TestPoint; TestPoint_Pad_D1.5mm
-8V: TestPoint; TestPoint_Pad_D1.5mm
C1, C2, C4, C6: 10u; C_1206_3216Metric_Pad1.33x1.80mm_HandSolder
C3, C5, C8, C11: 100u; C_Radial_D5.0mm_H11.0mm_P2.00mm
C7, C10: 1u; C_0805_2012Metric_Pad1.18x1.45mm_HandSolder
C9, C12: 0.1u; C_0603_1608Metric_Pad1.08x0.95mm_HandSolder
D1, D2, D3, D4: LED; LED_0603_1608Metric
F1: Polyfuse; Fuse_Bourns_MF-RHT550
F2, F3: Polyfuse_Small; Fuse_1812_4532Metric
H1, H2, H3, H4: MountingHole_Pad; MountingHole_3.2mm_M3_Pad
J1, J14: Screw_Terminal_01x02; TerminalBlock_bornier-2_P5.08mm
J2: Conn_01x03; JST_XH_B3B-XH-A_1x03_P2.50mm_Vertical
J3, J4, J5, J6, J7, J8, J9, J10, J12, J13: Conn_01x02; JST_XH_B2B-XH-A_1x02_P2.50mm_Vertical
J11: Conn_01x04; JST_XH_B4B-XH-A_1x04_P2.50mm_Vertical
LDO3.3+, LDO8+, LDO8-: TO-252-3_TabPin2
LDO5+: TO-263-7_TabPin4
R1: 100K; R_0402_1005Metric_Pad0.72x0.64mm_HandSolder
R2, R11: 3K; R_0603_1608Metric_Pad0.98x0.95mm_HandSolder
R3: 680; R_0603_1608Metric_Pad0.98x0.95mm_HandSolder
R4, R5, R6, R7, R8: 1K; R_0603_1608Metric_Pad0.98x0.95mm_HandSolder
R9, R10: 470; R_0603_1608Metric_Pad0.98x0.95mm_HandSolder
RF1, RF2: 10K; R_0805_2012Metric_Pad1.20x1.40mm_HandSolder
TEMP: Conn_01x02; JST_XH_B2B-XH-A_1x02_P2.50mm_Vertical
TH1, TH2: Thermistor_NTC; R_0805_2012Metric_Pad1.20x1.40mm_HandSolder
UR+5V, UR+12V: TestPoint; TestPoint_Pad_D1.5mm
UR-12V: TestPoint; TestPoint_Pad_D1.5mm

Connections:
+3.3V: +3.3V.1, C2.1, D1.2 (A), J3.2, J4.2, J5.2, LDO3.3+.3 (OUT)
+5V: +5V.1, C6.1, D4.2 (A), J10.2, J11.3, J11.4, J14.2, LDO5+.5 (VOUT), LDO5+.6 (VOUT), R11.2, RF1.1, RF2.1
+8V: +8V.1, C9.1, D2.2 (A), J6.2, J7.2, J8.2, LDO8+.3 (OUT)
-8V: -8V.1, C12.1, D3.1 (K), J9.2, LDO8-.3 (OUT)
GND: C1.2, C2.2, C3.2, C4.2, C5.2, C6.2, C7.2, C8.2, C9.2, C10.2, C11.2, C12.2, H1.1, H2.1, H3.1, H4.1, J1.1, J2.1, J3.1, J4.1, J5.1, J6.1, J7.1, J8.1, J9.1, J10.1, J11.1, J11.2, J12.1, J13.1, J14.1, LDO3.3+.2 (GND), LDO5+.4 (GND), LDO8+.2 (GND), LDO8-.2 (GND), R3.1, R4.2, R5.2, R8.2, R9.2, R10.2, TH1.2, TH2.2
unnamed: D1.1 (K), R4.1, R8.1
unnamed: D4.1 (K), R5.1
unnamed: D2.1 (K), R6.1
unnamed: D3.2 (A), R7.1
unnamed: F1.1, J1.2
unnamed: F3.1, J2.2
unnamed: F2.1, J2.3
unnamed: LDO5+.7 (ADJ), R2.1, R3.2
unnamed: LDO5+.1 (EN), R1.2
unnamed: R6.2, R9.1
unnamed: R7.2, R10.1
unnamed: R2.2, R11.1
TEMP_1: RF1.2, TEMP.1, TH1.1
TEMP_2: RF2.2, TEMP.2, TH2.1
UR_+5V: C1.1, C3.1, C4.1, C5.1, F1.2, LDO3.3+.1 (IN), LDO5+.2 (VIN), LDO5+.3 (VIN), R1.1, UR+5V.1
UR_+12V: C7.1, C8.1, F3.2, J12.2, J13.2, LDO8+.1 (IN), UR+12V.1
UR_-12V: C10.1, C11.1, F2.2, LDO8-.1 (IN), UR-12V.1

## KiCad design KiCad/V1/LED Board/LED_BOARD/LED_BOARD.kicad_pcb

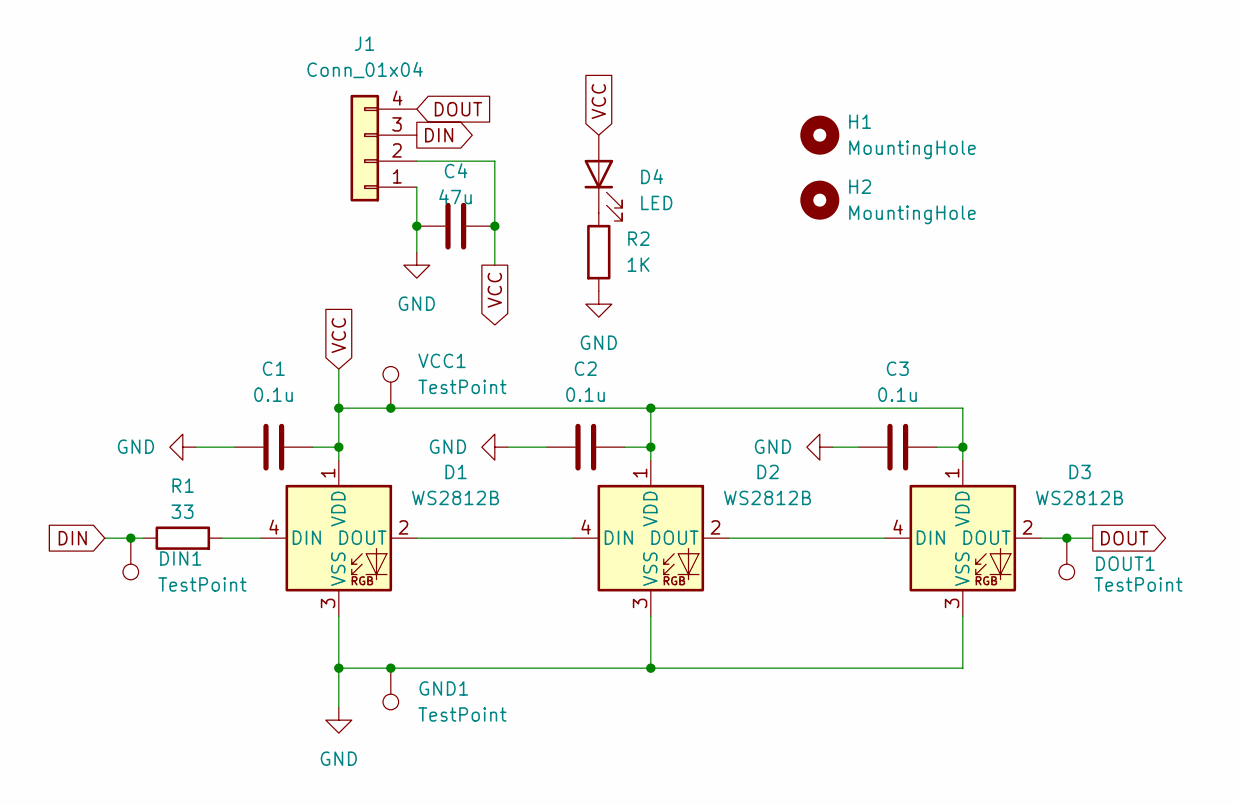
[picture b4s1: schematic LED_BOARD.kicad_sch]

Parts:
C1, C2, C3: 0.1u; C_0603_1608Metric_Pad1.08x0.95mm_HandSolder
C4: 47u; CP_Radial_D5.0mm_P2.00mm
D1, D2, D3: WS2812B; LED_WS2812B_PLCC4_5.0x5.0mm_P3.2mm
D4: LED; LED_0603_1608Metric_Pad1.05x0.95mm_HandSolder
DIN1: TestPoint; TestPoint_Pad_D1.5mm
DOUT1: TestPoint; TestPoint_Pad_D1.5mm
GND1: TestPoint; TestPoint_Pad_D1.5mm
H1, H2: MountingHole; MountingHole_3.2mm_M3
J1: Conn_01x04; PinSocket_1x04_P2.54mm_Vertical
R1: 33; R_0402_1005Metric_Pad0.72x0.64mm_HandSolder
R2: 1K; R_0603_1608Metric_Pad0.98x0.95mm_HandSolder
VCC1: TestPoint; TestPoint_Pad_D1.5mm

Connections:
DIN: DIN1.1, J1.3, R1.1
DOUT: D3.2 (DOUT), DOUT1.1, J1.4
GND: C1.1, C2.1, C3.1, C4.1, D1.3 (VSS), D2.3 (VSS), D3.3 (VSS), GND1.1, J1.1, R2.2
unnamed: D1.4 (DIN), R1.2
unnamed: D1.2 (DOUT), D2.4 (DIN)
unnamed: D2.2 (DOUT), D3.4 (DIN)
unnamed: D4.1 (K), R2.1
VCC: C1.2, C2.2, C3.2, C4.2, D1.1 (VDD), D2.1 (VDD), D3.1 (VDD), D4.2 (A), J1.2, VCC1.1

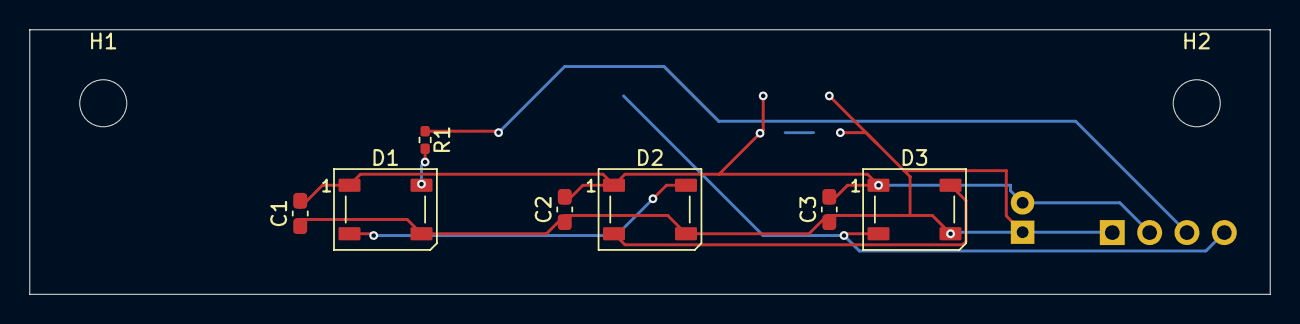
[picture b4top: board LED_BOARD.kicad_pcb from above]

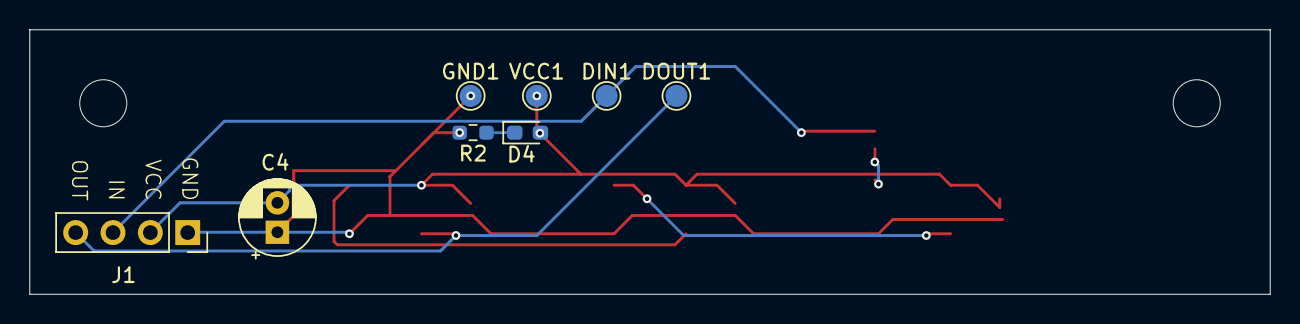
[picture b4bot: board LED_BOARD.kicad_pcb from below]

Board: 2 copper layers, 84.4 x 18.0 mm, 17 parts (8 on the bottom side), 8 nets.

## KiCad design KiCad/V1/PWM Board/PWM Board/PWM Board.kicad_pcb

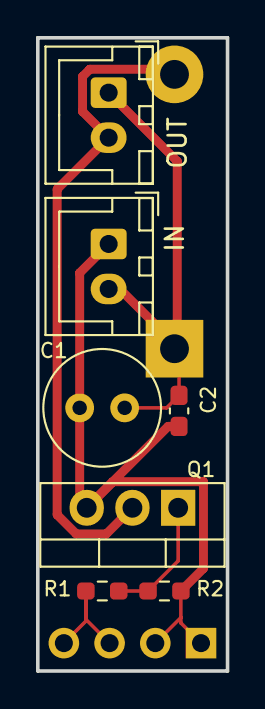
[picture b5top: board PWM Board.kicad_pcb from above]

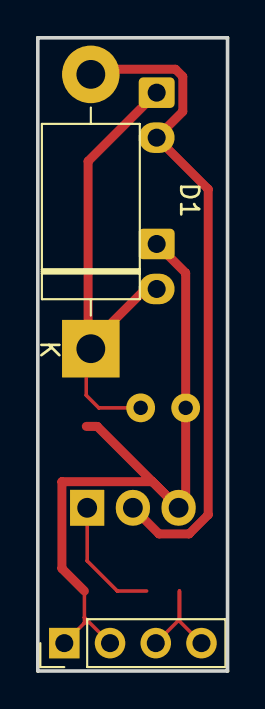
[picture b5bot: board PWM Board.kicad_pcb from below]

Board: 2 copper layers, 10.5 x 35.2 mm, 9 parts (2 on the bottom side), 5 nets.

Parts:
C1: 47u; C_Radial_D6.3mm_H11.0mm_P2.50mm
C2: 0.1u; C_0603_1608Metric_Pad1.08x0.95mm_HandSolder
D1: 1N5822; D_DO-201AD_P15.24mm_Horizontal
IN: Conn_01x02; JST_XH_B2B-XH-A_1x02_P2.50mm_Vertical
J1: Conn_01x04; PinHeader_1x04_P2.54mm_Vertical
OUT: Conn_01x02; JST_XH_B2B-XH-A_1x02_P2.50mm_Vertical
Q1: IRLZ44N; TO-220-3_Vertical
R1: 100; R_0603_1608Metric_Pad0.98x0.95mm_HandSolder
R2: 10K; R_0603_1608Metric_Pad0.98x0.95mm_HandSolder

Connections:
GND: C1.2, C2.2, IN.1, J1.1, J1.2, Q1.3 (S), R2.1
unnamed: D1.2 (A), OUT.2, Q1.2 (D)
unnamed: C1.1, C2.1, D1.1 (K), IN.2, OUT.1
unnamed: J1.3, J1.4, R1.1
unnamed: Q1.1 (G), R1.2, R2.2

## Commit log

2024-10-12 EMF Considerations
2024-10-13 Reorganised
2024-10-15 V2 CAD Proposed Changes
2024-10-31 CAD and Reports
    CAD V2 is mostly done. Lots of additional CAD files have been downloaded and added.
    Reports for the front panel and a CAD progress update have been made. A sample tracker has been created to track all sample requests and free products obtained.
2024-12-16 progress updates
2024-12-23 Front panel CAD & datasheets
2025-01-18 STM32CUBE Testing
    STM32CUBE "Hello World" completed
    STM32CUBE LCD SPI driver tested and implemented
    STM32CUBE TouchGFX tested and implemented - ready for custom TouchGFX application
